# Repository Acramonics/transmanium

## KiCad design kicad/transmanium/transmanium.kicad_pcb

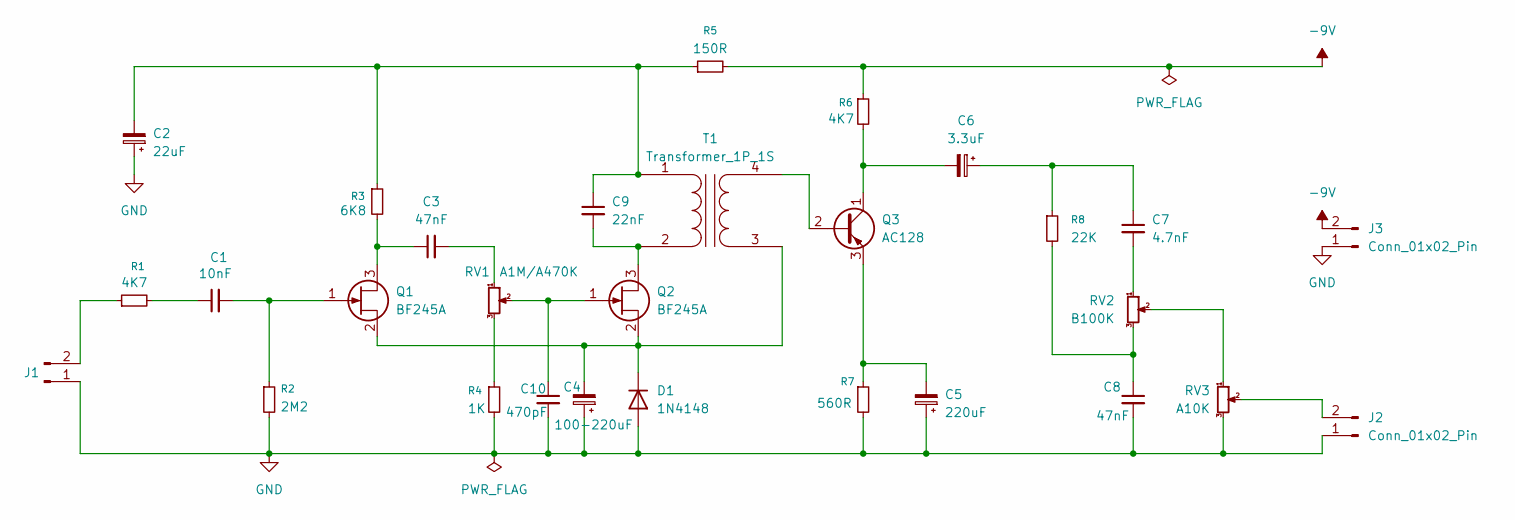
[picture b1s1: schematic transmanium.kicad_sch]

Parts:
C1: 10nF; C_Rect_L7.2mm_W3.0mm_P5.00mm_FKS2_FKP2_MKS2_MKP2
C2: 22uF; CP_Radial_D8.0mm_P3.50mm
C3, C8: 47nF; C_Rect_L7.2mm_W3.0mm_P5.00mm_FKS2_FKP2_MKS2_MKP2
C4: 100-220uF; CP_Radial_D8.0mm_P3.50mm
C5: 220uF; CP_Radial_D8.0mm_P3.50mm
C6: 3.3uF; CP_Radial_D8.0mm_P3.50mm
C7: 4.7nF; C_Rect_L7.2mm_W3.0mm_P5.00mm_FKS2_FKP2_MKS2_MKP2
C9: 22nF; C_Rect_L7.2mm_W3.0mm_P5.00mm_FKS2_FKP2_MKS2_MKP2
C10: 470pF; C_Rect_L7.2mm_W3.0mm_P5.00mm_FKS2_FKP2_MKS2_MKP2
D1: 1N4148; D_DO-35_SOD27_P7.62mm_Horizontal
J1, J2, J3: Conn_01x02_Pin; Molex_KK-254_AE-6410-02A_1x02_P2.54mm_Vertical
Q1, Q2: BF245A; TO-92_Inline
Q3: AC128; TO-1-3
R1, R6: 4K7; R_Axial_DIN0207_L6.3mm_D2.5mm_P10.16mm_Horizontal
R2: 2M2; R_Axial_DIN0207_L6.3mm_D2.5mm_P10.16mm_Horizontal
R3: 6K8; R_Axial_DIN0207_L6.3mm_D2.5mm_P10.16mm_Horizontal
R4: 1K; R_Axial_DIN0207_L6.3mm_D2.5mm_P10.16mm_Horizontal
R5: 150R; R_Axial_DIN0207_L6.3mm_D2.5mm_P10.16mm_Horizontal
R7: 560R; R_Axial_DIN0207_L6.3mm_D2.5mm_P10.16mm_Horizontal
R8: 22K; R_Axial_DIN0207_L6.3mm_D2.5mm_P10.16mm_Horizontal
RV1: A1M/A470K; Potentiometer_Alps_RK09L_Single_Vertical
RV2: B100K; Potentiometer_Alps_RK09L_Single_Vertical
RV3: A10K; Potentiometer_Alps_RK09L_Single_Vertical
T1: Transformer_1P_1S; Transformer_LT722

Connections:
-9V: J3.2, R5.2, R6.1
GND: C2.1, C4.1, C5.1, C8.2, C10.2, D1.2 (A), J1.1, J2.1, J3.1, R2.2, R4.2, R7.2, RV3.3
unnamed: C1.1, R1.2
unnamed: C3.2, RV1.1
unnamed: C6.1, C7.1, R8.1
unnamed: C7.2, RV2.1
unnamed: C8.1, R8.2, RV2.3
unnamed: C4.2, D1.1 (K), Q1.2 (S), Q2.2 (S), T1.3 (SA)
unnamed: J1.2, R1.1
unnamed: J2.2, RV3.2
unnamed: C3.1, Q1.3 (D), R3.2
unnamed: C1.2, Q1.1 (G), R2.1
unnamed: C9.2, Q2.3 (D), T1.2 (AB)
unnamed: C10.1, Q2.1 (G), RV1.2
unnamed: Q3.2 (B), T1.4 (SB)
unnamed: C6.2, Q3.1 (C), R6.2
unnamed: C5.2, Q3.3 (E), R7.1
unnamed: R4.1, RV1.3
unnamed: RV2.2, RV3.1
unnamed: C2.2, C9.1, R3.1, R5.1, T1.1 (AA)

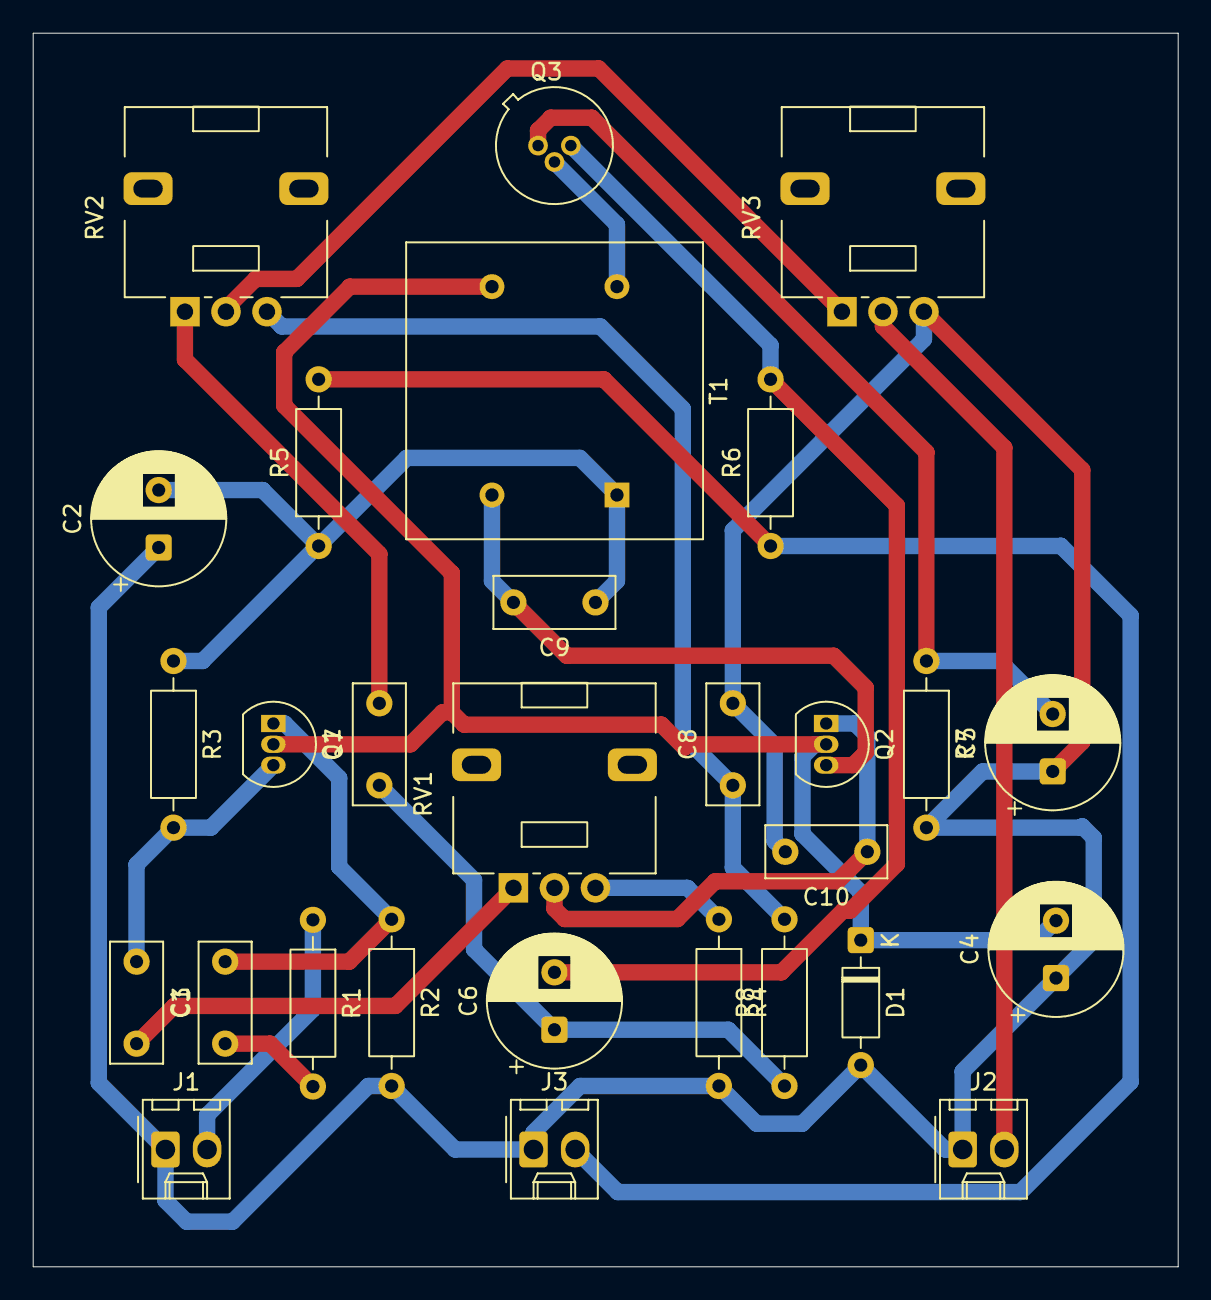
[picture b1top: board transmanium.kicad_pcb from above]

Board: 2 copper layers, 69.8 x 75.2 mm, 29 parts (0 on the bottom side), 20 nets.

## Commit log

2025-10-13 First proper version
2025-11-01 Changed directory structure
